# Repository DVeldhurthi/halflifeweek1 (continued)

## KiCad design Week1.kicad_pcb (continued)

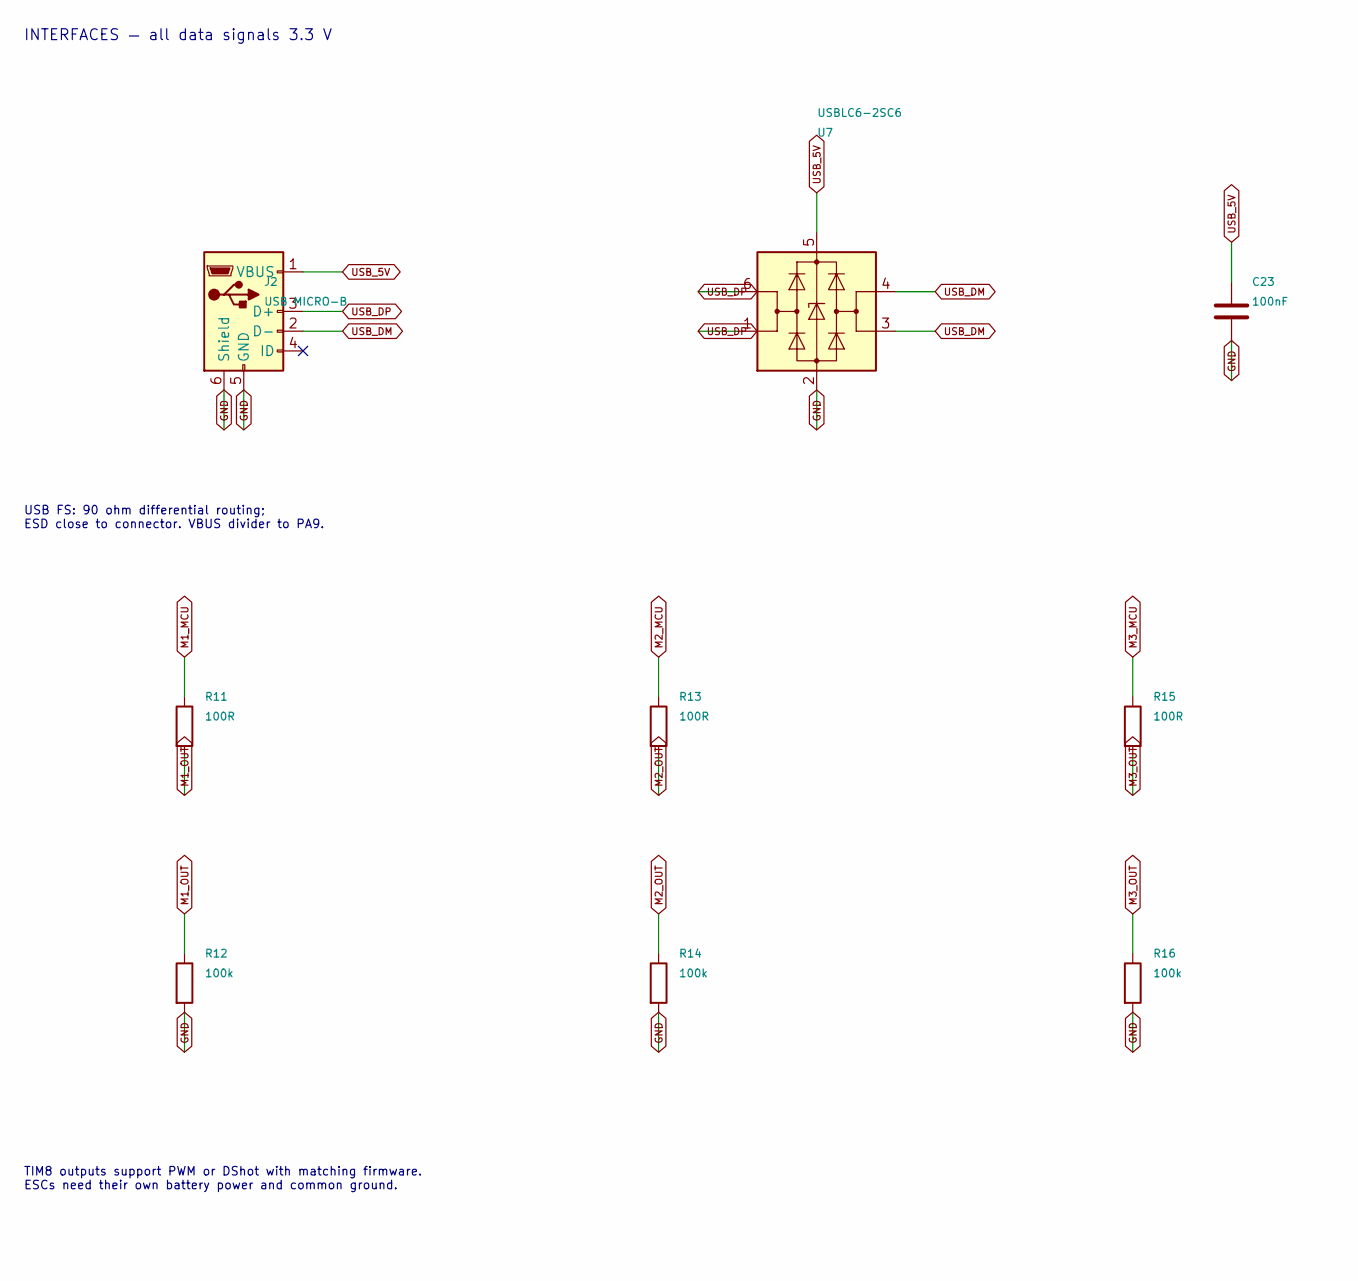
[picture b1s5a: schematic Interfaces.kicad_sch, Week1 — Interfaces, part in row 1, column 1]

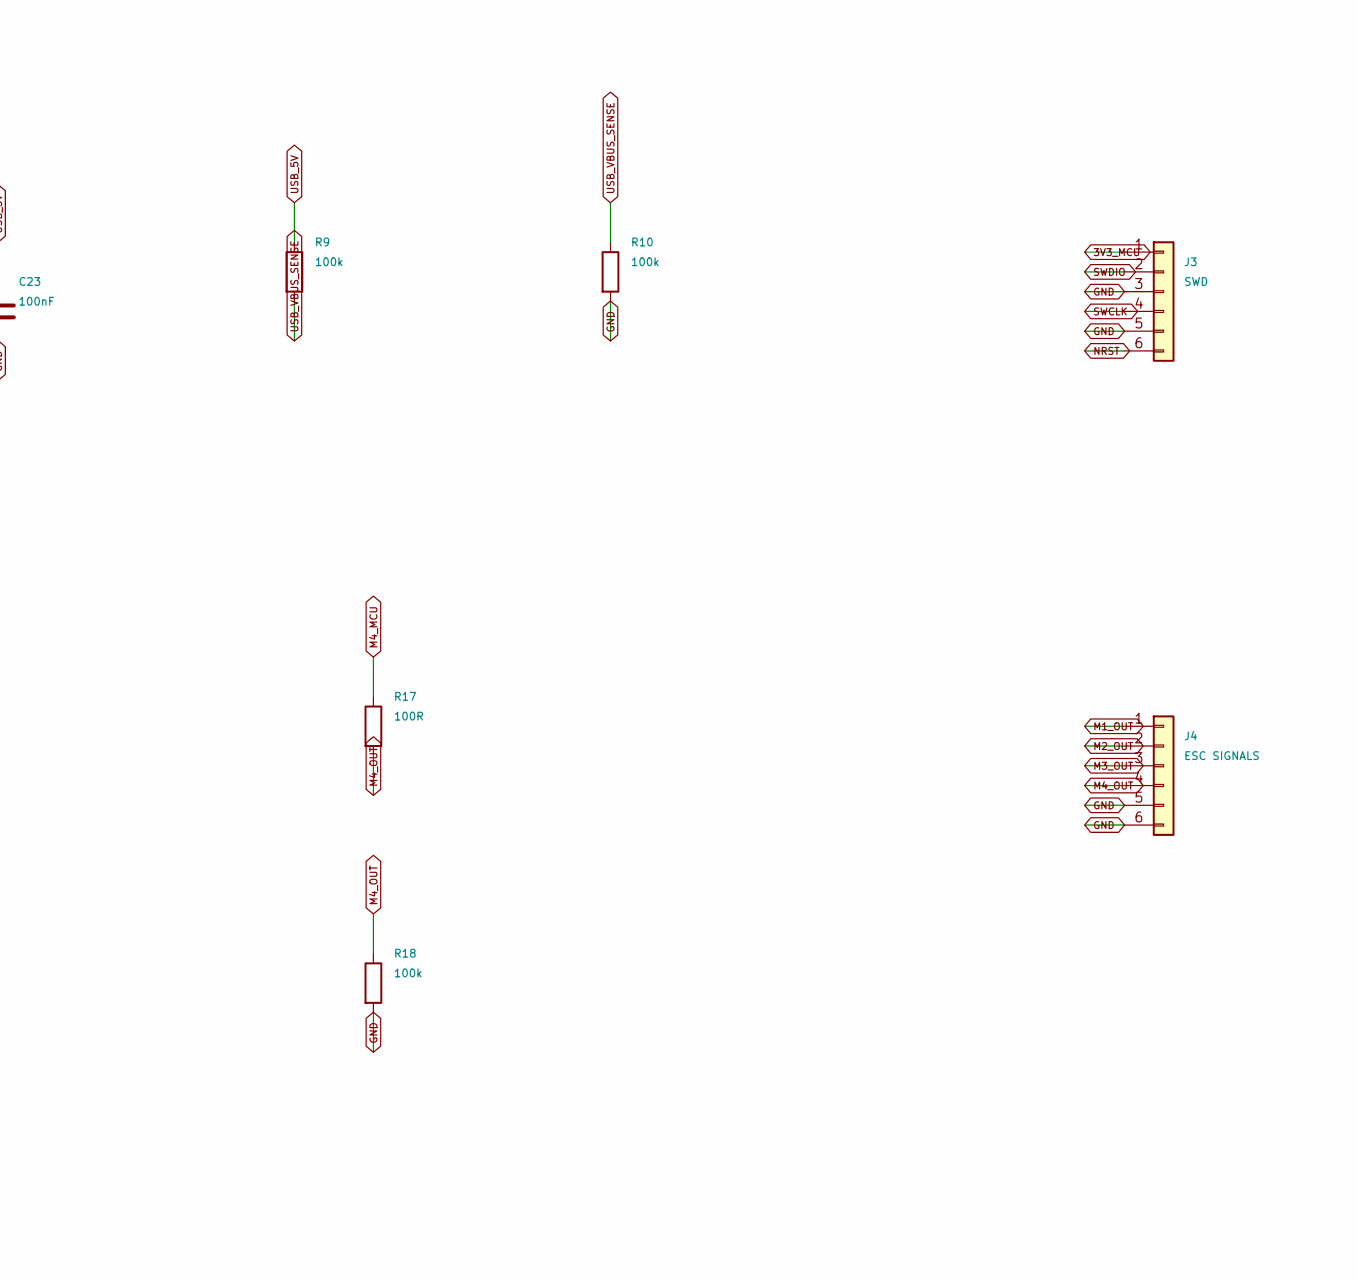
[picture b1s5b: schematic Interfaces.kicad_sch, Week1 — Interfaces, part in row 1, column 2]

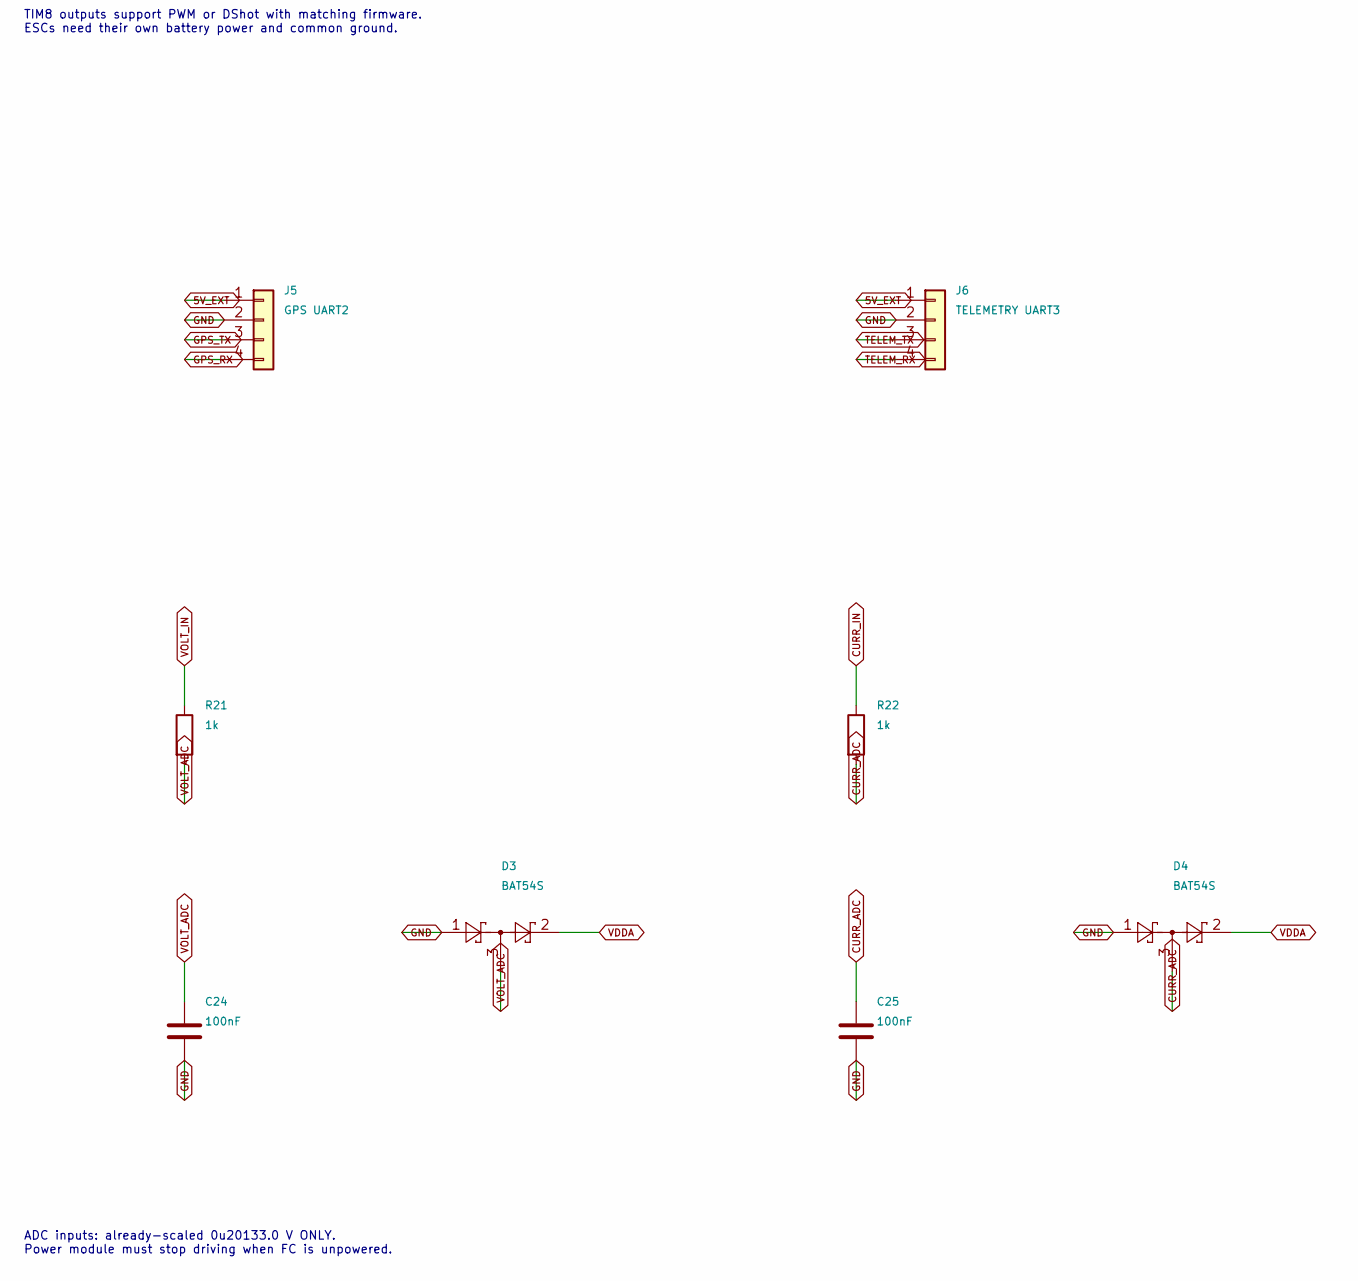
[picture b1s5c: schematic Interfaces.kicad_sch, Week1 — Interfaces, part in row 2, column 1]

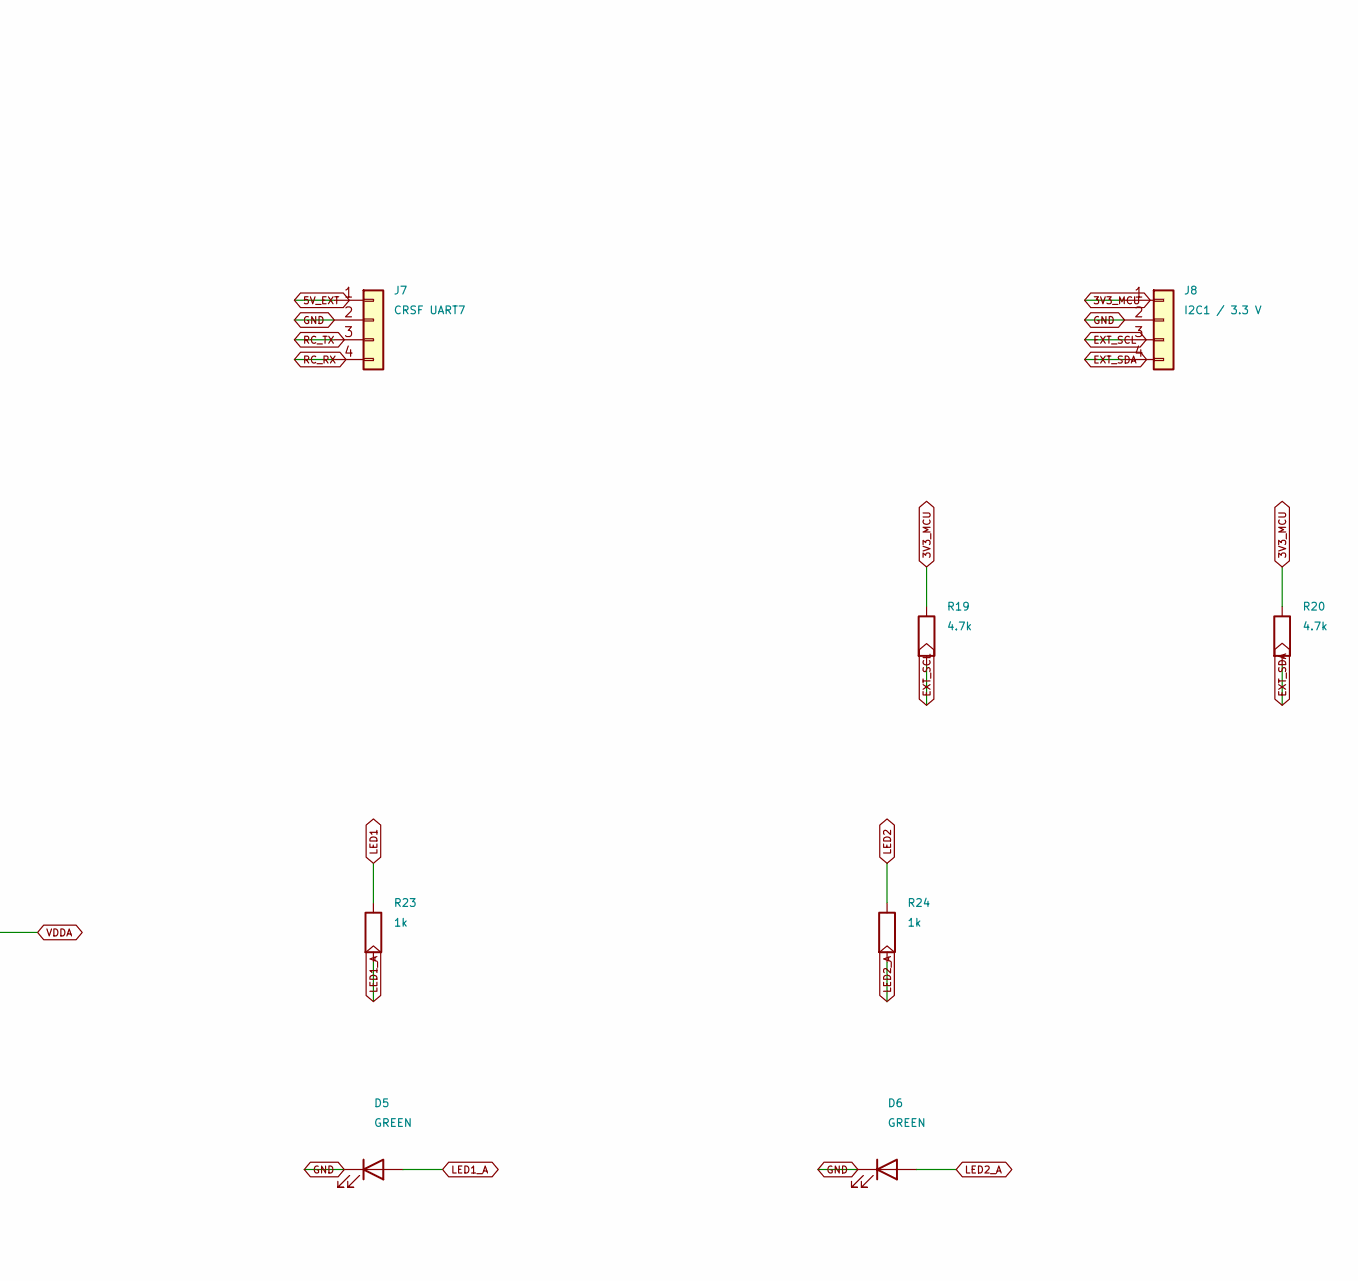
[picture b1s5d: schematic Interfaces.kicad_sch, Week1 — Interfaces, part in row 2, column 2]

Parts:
C23, C24, C25: 100nF; C_0603_1608Metric
D3, D4: BAT54S; SOT-23
D5, D6: GREEN; LED_0603_1608Metric
J2: USB MICRO-B; USB_Micro-B_Amphenol_10118194_Horizontal
J3: SWD; PinHeader_1x06_P1.27mm_Vertical
J4: ESC SIGNALS; JST_GH_SM06B-GHS-TB_1x06-1MP_P1.25mm_Horizontal
J5: GPS UART2; JST_GH_SM04B-GHS-TB_1x04-1MP_P1.25mm_Horizontal
J6: TELEMETRY UART3; JST_GH_SM04B-GHS-TB_1x04-1MP_P1.25mm_Horizontal
J7: CRSF UART7; JST_GH_SM04B-GHS-TB_1x04-1MP_P1.25mm_Horizontal
J8: I2C1 / 3.3 V; JST_GH_SM04B-GHS-TB_1x04-1MP_P1.25mm_Horizontal
R9, R10, R12, R14, R16, R18: 100k; R_0603_1608Metric
R11, R13, R15, R17: 100R; R_0603_1608Metric
R19, R20: 4.7k; R_0603_1608Metric
R21, R22, R23, R24: 1k; R_0603_1608Metric
U7: USBLC6-2SC6; SOT-23-6

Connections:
3V3_MCU: J3.1, J8.1, R19.1, R20.1; also elsewhere on the board
5V_EXT: J5.1, J6.1, J7.1; also elsewhere on the board
CURR_ADC: C25.1, D4.3, R22.2; also elsewhere on the board
CURR_IN: R22.1; also elsewhere on the board
EXT_SCL: J8.3, R19.2; also elsewhere on the board
EXT_SDA: J8.4, R20.2; also elsewhere on the board
GND: C23.2, C24.2, C25.2, D3.1, D4.1, D5.1 (K), D6.1 (K), J2.5 (GND), J2.6 (Shield), J3.3, J3.5, J4.5, J4.6, J5.2, J6.2, J7.2, J8.2, R10.2, R12.2, R14.2, R16.2, R18.2, U7.2 (GND); also elsewhere on the board
GPS_RX: J5.4; also elsewhere on the board
GPS_TX: J5.3; also elsewhere on the board
LED1: R23.1; also elsewhere on the board
LED1_A: D5.2 (A), R23.2
LED2: R24.1; also elsewhere on the board
LED2_A: D6.2 (A), R24.2
M1_MCU: R11.1; also elsewhere on the board
M1_OUT: J4.1, R11.2, R12.1
M2_MCU: R13.1; also elsewhere on the board
M2_OUT: J4.2, R13.2, R14.1
M3_MCU: R15.1; also elsewhere on the board
M3_OUT: J4.3, R15.2, R16.1
M4_MCU: R17.1; also elsewhere on the board
M4_OUT: J4.4, R17.2, R18.1
NRST: J3.6; also elsewhere on the board
RC_RX: J7.4; also elsewhere on the board
RC_TX: J7.3; also elsewhere on the board
SWCLK: J3.4; also elsewhere on the board
SWDIO: J3.2; also elsewhere on the board
TELEM_RX: J6.4; also elsewhere on the board
TELEM_TX: J6.3; also elsewhere on the board
USB_5V: C23.1, J2.1 (VBUS), R9.1, U7.5 (VBUS); also elsewhere on the board
USB_DM: J2.2 (D-), U7.3 (I/O2), U7.4 (I/O2); also elsewhere on the board
USB_DP: J2.3 (D+), U7.1 (I/O1), U7.6 (I/O1); also elsewhere on the board
USB_VBUS_SENSE: R9.2, R10.1; also elsewhere on the board
VDDA: D3.2, D4.2; also elsewhere on the board
VOLT_ADC: C24.1, D3.3, R21.2; also elsewhere on the board
VOLT_IN: R21.1; also elsewhere on the board

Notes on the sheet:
INTERFACES — all data signals 3.3 V
USB FS: 90 ohm differential routing; ESD close to connector. VBUS divider to PA9.
TIM8 outputs support PWM or DShot with matching firmware. ESCs need their own battery power and common ground.
ADC inputs: already-scaled 0u20133.0 V ONLY. Power module must stop driving when FC is unpowered.

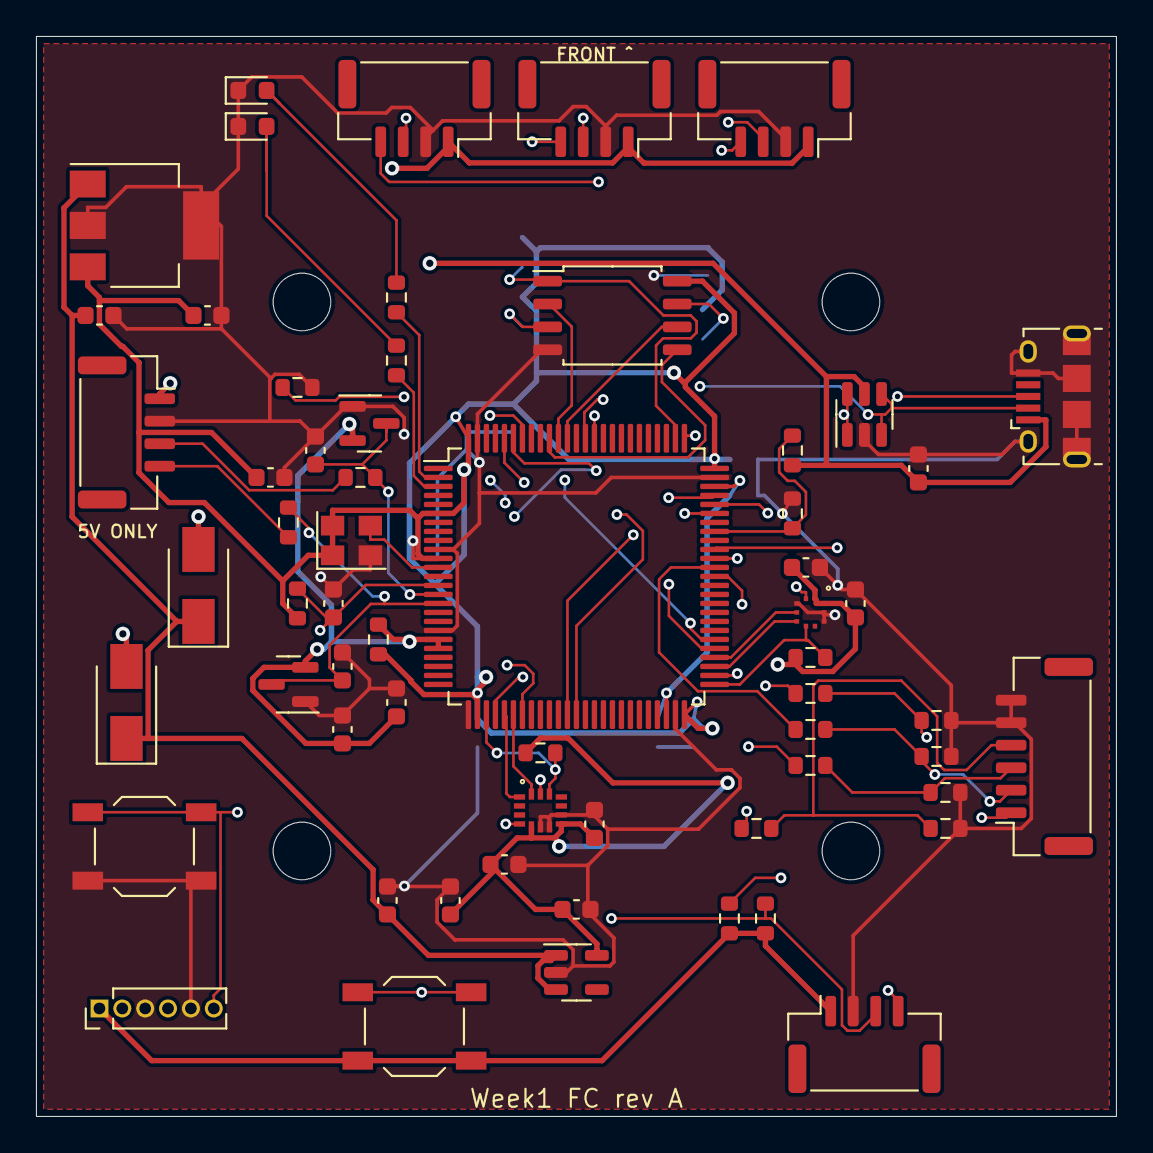
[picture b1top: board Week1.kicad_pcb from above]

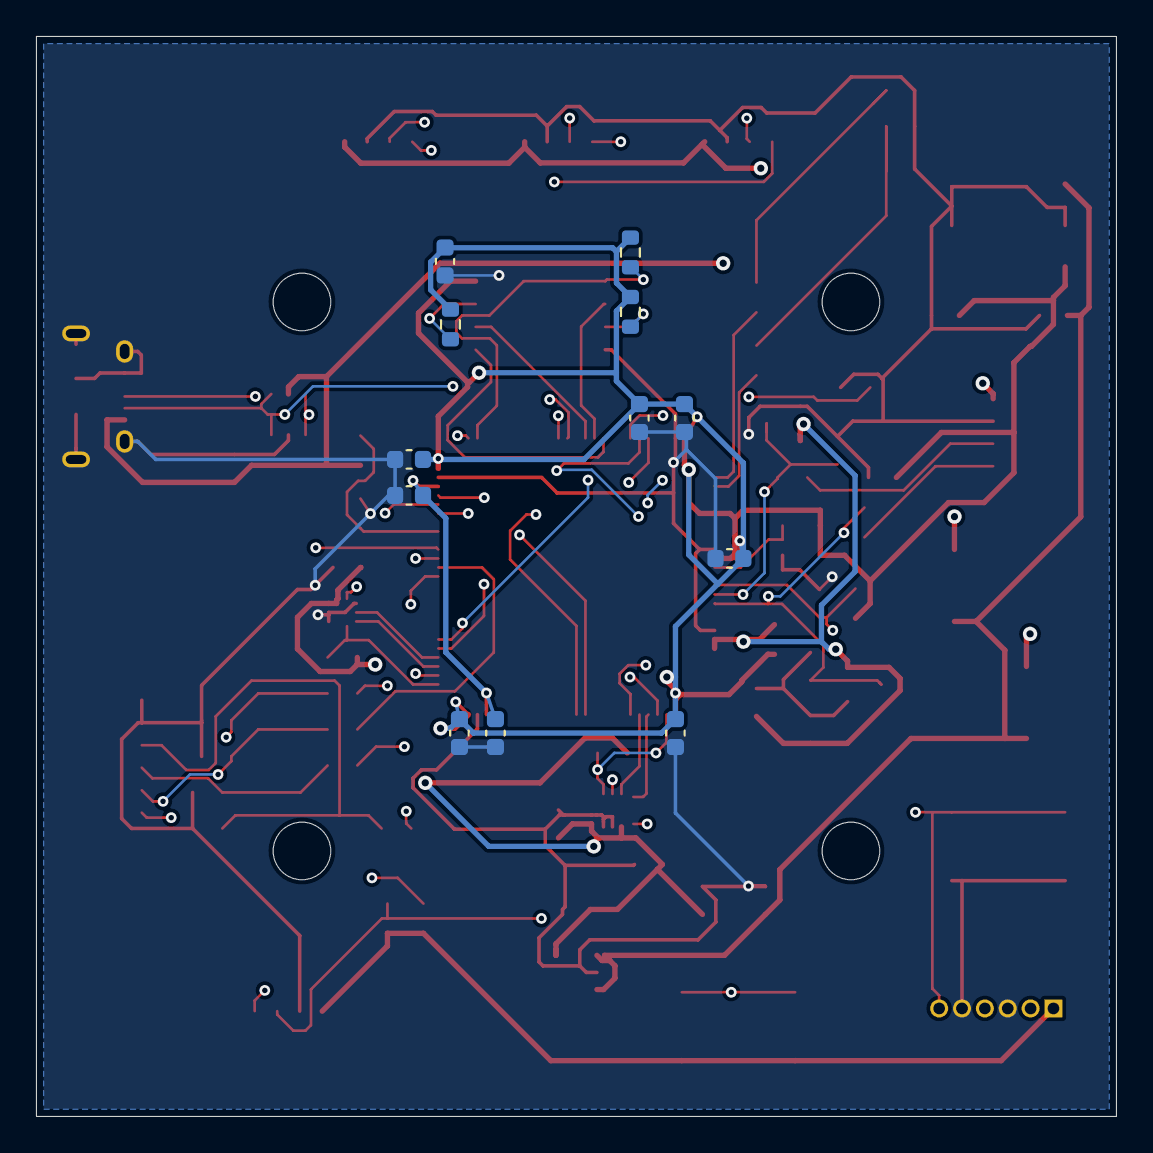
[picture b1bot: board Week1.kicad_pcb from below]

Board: 4 copper layers, 60.0 x 60.0 mm, 77 parts (12 on the bottom side), 55 nets.

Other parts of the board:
H1, H2, H3, H4: MountingHole_3.2mm_M3
